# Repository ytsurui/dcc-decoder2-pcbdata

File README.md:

# ATtiny1606 DCC Decoder PCB Data

NMRA規格の信号を受信して動作する、DCCデコーダの基板設計データです。

主にNゲージ鉄道模型への搭載を想定して小型に設計しております。

## すべての基板に共通するスペック
  * 走行用モーター出力
  * BEMF読み取りによるフィードバック制御に対応
  * 最大7ファンクション出力
  * BiDi (Railcom) 出力
  * (試験的実装) Asymmetric DCCの認識回路
  
くわしくは、各基板のデータをご覧ください。
  * [K3066RA](docs/readme-K3066.md)
  * [K3057RA](docs/readme-K3057.md)
  * [M02F7RA Roomlight-N](docs/readme-roomlight-n.md)
  * [M02F7RA](docs/readme-normal.md)

## 閲覧・編集に必要なCAD (開発環境)
  * KiCad Version (5.1.9)-1 (またはそれ以降)

## 回路図

  * [v2021-04](https://github.com/ytsurui/dcc-decoder2-pcbdata/releases/tag/v2021-04)

## 対応するファームウェア
  * [ATtiny1606 DCC Decoder Firmware](https://github.com/ytsurui/dcc-decoder2-firmware)

このリポジトリに含まれる、すべての種類のデコーダが上記のファームウェアで動くように設計されています。

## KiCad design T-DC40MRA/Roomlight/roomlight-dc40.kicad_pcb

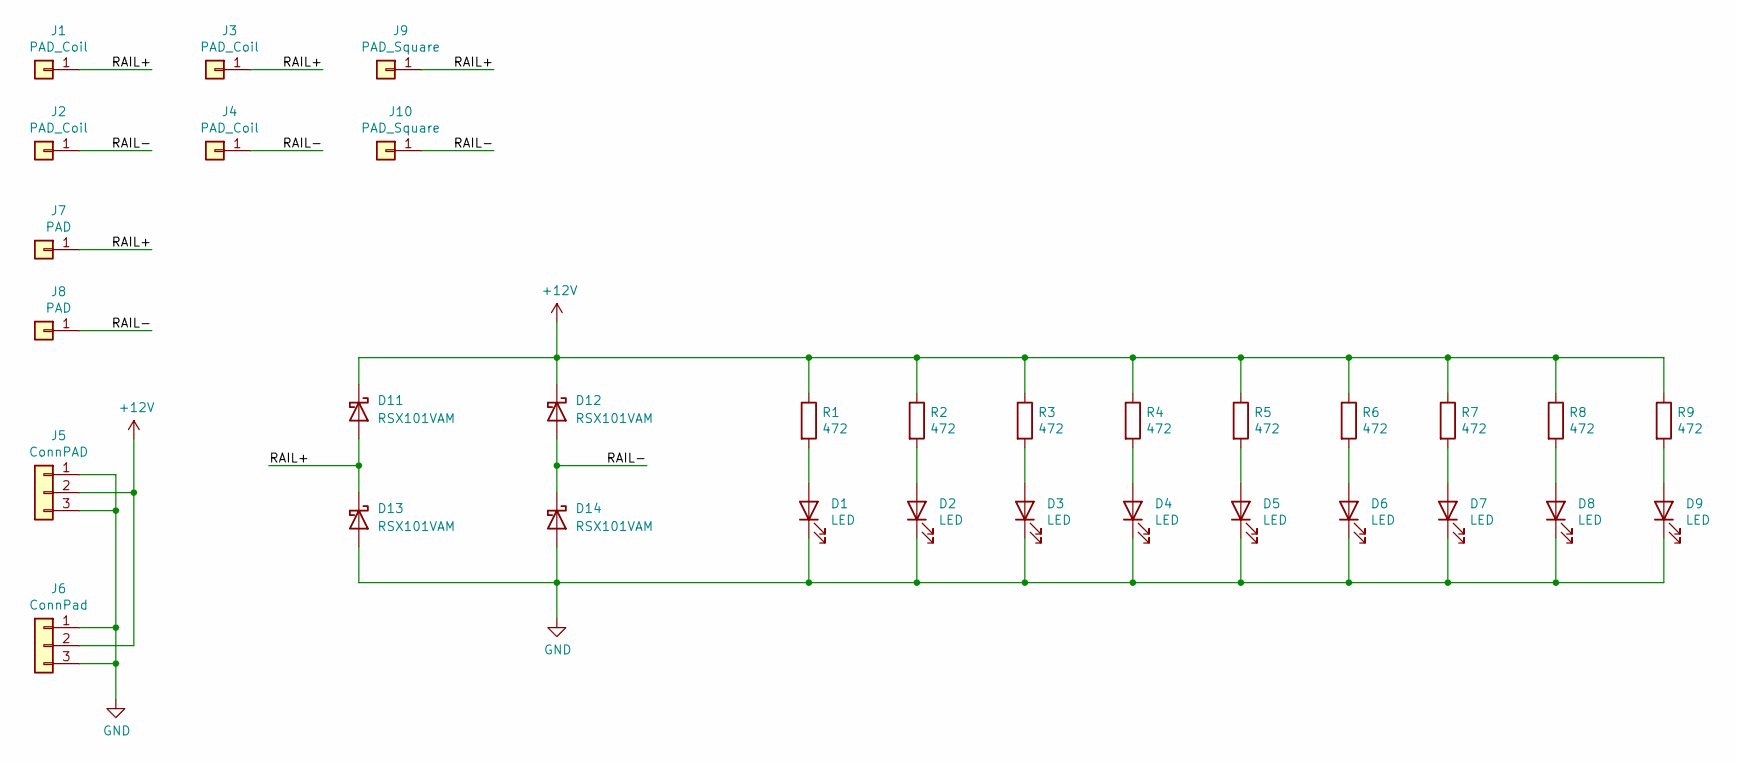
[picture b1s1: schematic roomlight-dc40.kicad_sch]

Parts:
D1, D2, D3, D4, D5, D6, D7, D8, D9: LED; LED_1608_SLIMPAD
D11, D12, D13, D14: RSX101VAM; TUMD2M
J1, J2, J3, J4: PAD_Coil; PAD_COIL_1.3x1.3_NoHole
J5: ConnPAD; PCB_CONN_PAD_3pin_2.5mmx1.2mm_SMD
J6: ConnPad; PCB_CONN_PAD_3pin_2.5mmx1.2mm_SMD
J7, J8: PAD; PAD_1.0x1.8_SMD
J9, J10: PAD_Square; PAD_Square_1.3x1.3_Hole0.8
R1, R2, R3, R4, R5, R6, R7, R8, R9: 472; R_1608_20240411

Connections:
+12V: D11.1 (K), D12.1 (K), J5.2, J6.2, R1.1, R2.1, R3.1, R4.1, R5.1, R6.1, R7.1, R8.1, R9.1
/RAIL+: D11.2 (A), D13.1 (K), J1.1, J3.1, J7.1, J9.1
/RAIL-: D12.2 (A), D14.1 (K), J2.1, J4.1, J8.1, J10.1
GND: D1.1 (K), D2.1 (K), D3.1 (K), D4.1 (K), D5.1 (K), D6.1 (K), D7.1 (K), D8.1 (K), D9.1 (K), D13.2 (A), D14.2 (A), J5.1, J5.3, J6.1, J6.3
unnamed: D1.2 (A), R1.2
unnamed: D2.2 (A), R2.2
unnamed: D3.2 (A), R3.2
unnamed: D4.2 (A), R4.2
unnamed: D5.2 (A), R5.2
unnamed: D6.2 (A), R6.2
unnamed: D7.2 (A), R7.2
unnamed: D8.2 (A), R8.2
unnamed: D9.2 (A), R9.2

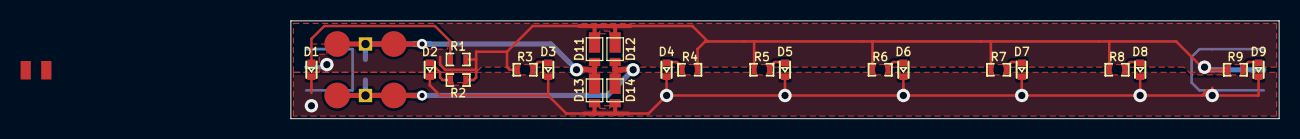
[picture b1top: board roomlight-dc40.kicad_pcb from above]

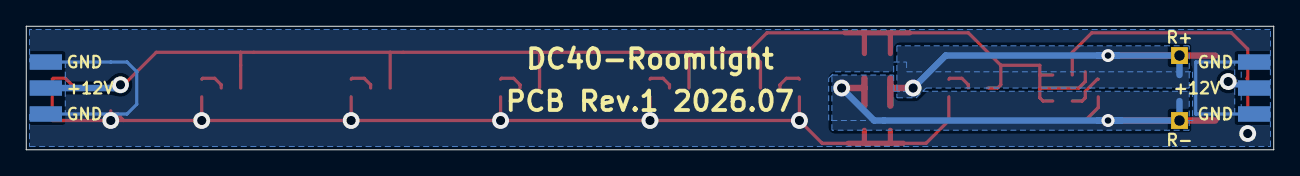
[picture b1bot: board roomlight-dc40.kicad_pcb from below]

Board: 2 copper layers, 96.0 x 9.5 mm, 32 parts (2 on the bottom side), 13 nets.

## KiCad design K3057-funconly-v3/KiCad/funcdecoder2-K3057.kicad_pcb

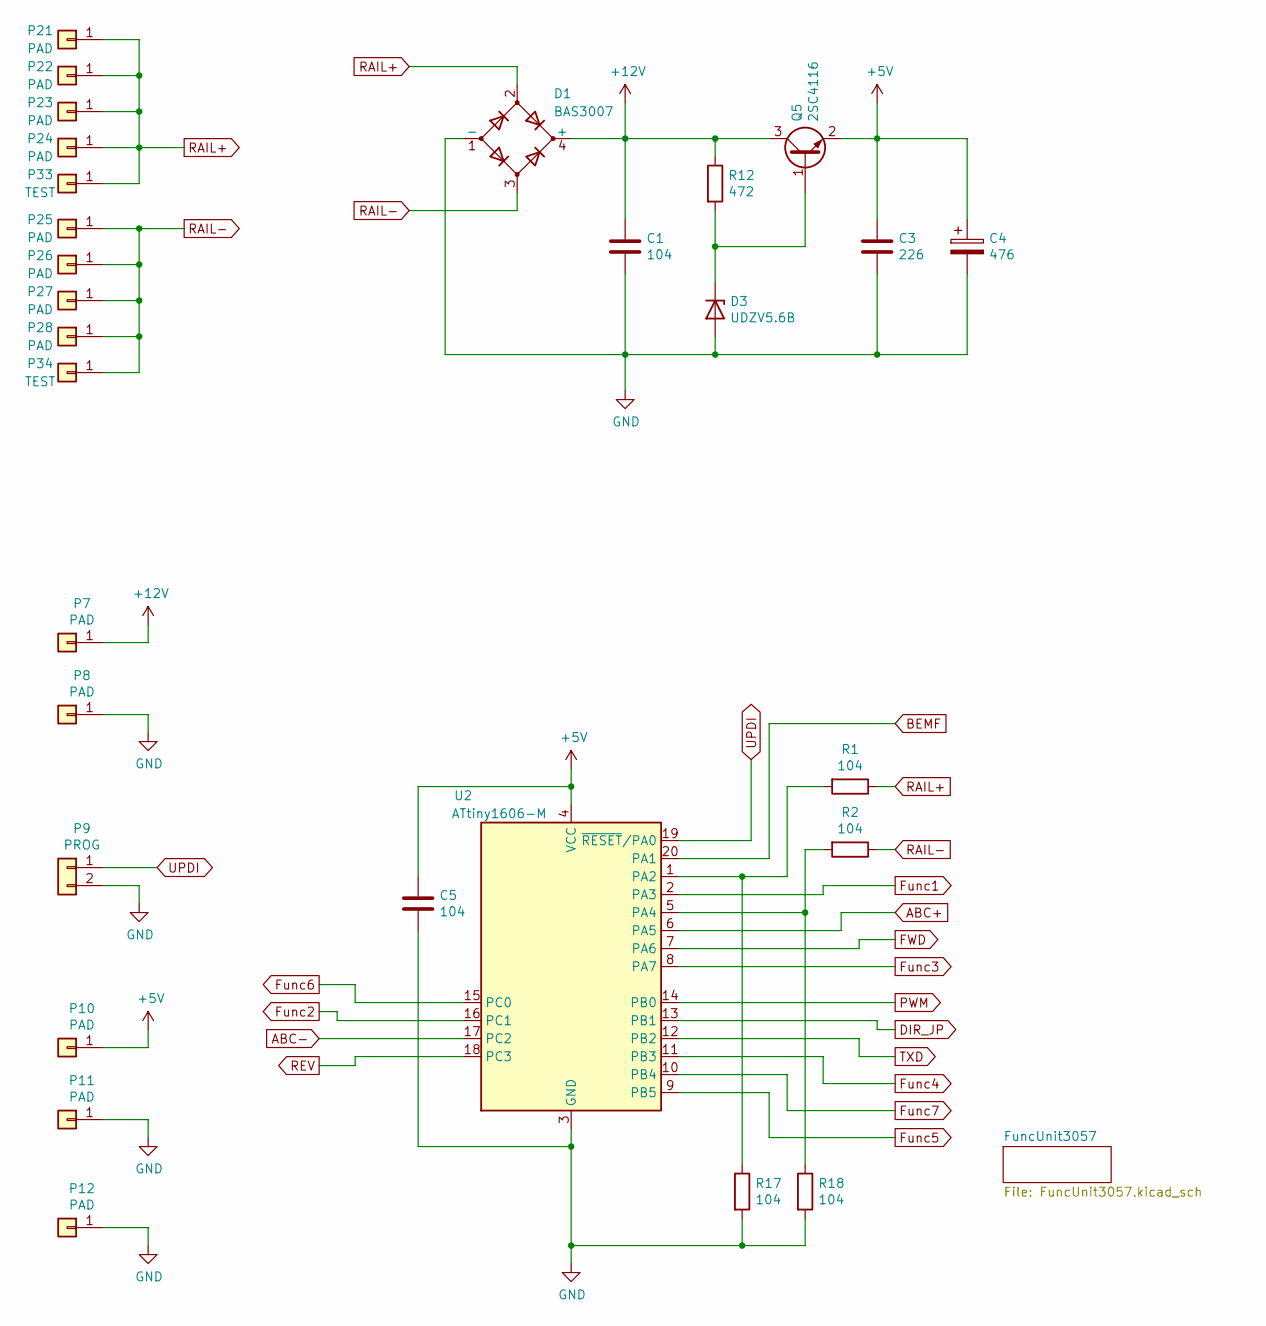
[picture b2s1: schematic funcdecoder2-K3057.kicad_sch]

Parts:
C1, C5: 104; C_1005_v4
C3: 226; C_1608_v4
C4: 476; CP_1608
D1: BAS3007; SOT-143
D3: UDZV5.6B; UMD2
P7: PAD; PAD_1.0x1.8_SMD
P8, P10: PAD; PAD_0.6x1.0_SMD
P9: PROG; PAD_PROG_2PIN_HOLE0.7
P11: PAD; PAD_0.5x1.2_SMD
P12: PAD; PAD_1.0x1.4_SMD
P21, P24, P25, P28: PAD; KATO_RAILPAD_3057_8mm
P22, P23, P26, P27: PAD; KATO_RAILPAD_3057_7mm
P33, P34: TEST; PAD_1.2x1.2_Hole0.7
Q5: 2SC4116; SC-70_v2
R1, R2, R17, R18: 104; R_1608_20240411
R12: 472; R_1608_20240411
U2: ATtiny1606-M; VQFN-20-1EP_3x3mm_P0.4mm_EP1.7x1.7mm

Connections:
+5V: C3.1, C4.1, C5.1, P10.1, Q5.2 (E), U2.4 (VCC)
+12V: C1.1, D1.4 (+), P7.1, Q5.3 (C), R12.1; also elsewhere on the board
ABC+: U2.6 (PA5)
ABC-: U2.17 (PC2)
BEMF: U2.20 (PA1)
DIR_JP: U2.13 (PB1); also elsewhere on the board
FWD: U2.7 (PA6)
Func1: U2.2 (PA3); also elsewhere on the board
Func2: U2.16 (PC1); also elsewhere on the board
Func3: U2.8 (PA7); also elsewhere on the board
Func4: U2.11 (PB3); also elsewhere on the board
Func5: U2.9 (PB5); also elsewhere on the board
Func6: U2.15 (PC0); also elsewhere on the board
Func7: U2.10 (PB4); also elsewhere on the board
GND: C1.2, C3.2, C4.2, C5.2, D1.1 (-), D3.2 (A), P8.1, P9.2, P11.1, P12.1, R17.2, R18.2, U2.3 (GND), U2.21 (GND); also elsewhere on the board
unnamed: D3.1 (K), Q5.1 (B), R12.2
unnamed: R1.2, R17.1, U2.1 (PA2)
unnamed: R2.2, R18.1, U2.5 (PA4)
PWM: U2.14 (PB0)
RAIL+: D1.2, P21.1, P22.1, P23.1, P24.1, P33.1, R1.1
RAIL-: D1.3, P25.1, P26.1, P27.1, P28.1, P34.1, R2.1
REV: U2.18 (PC3)
TXD: U2.12 (PB2)
UPDI: P9.1, U2.19 (~RESET/PA0)

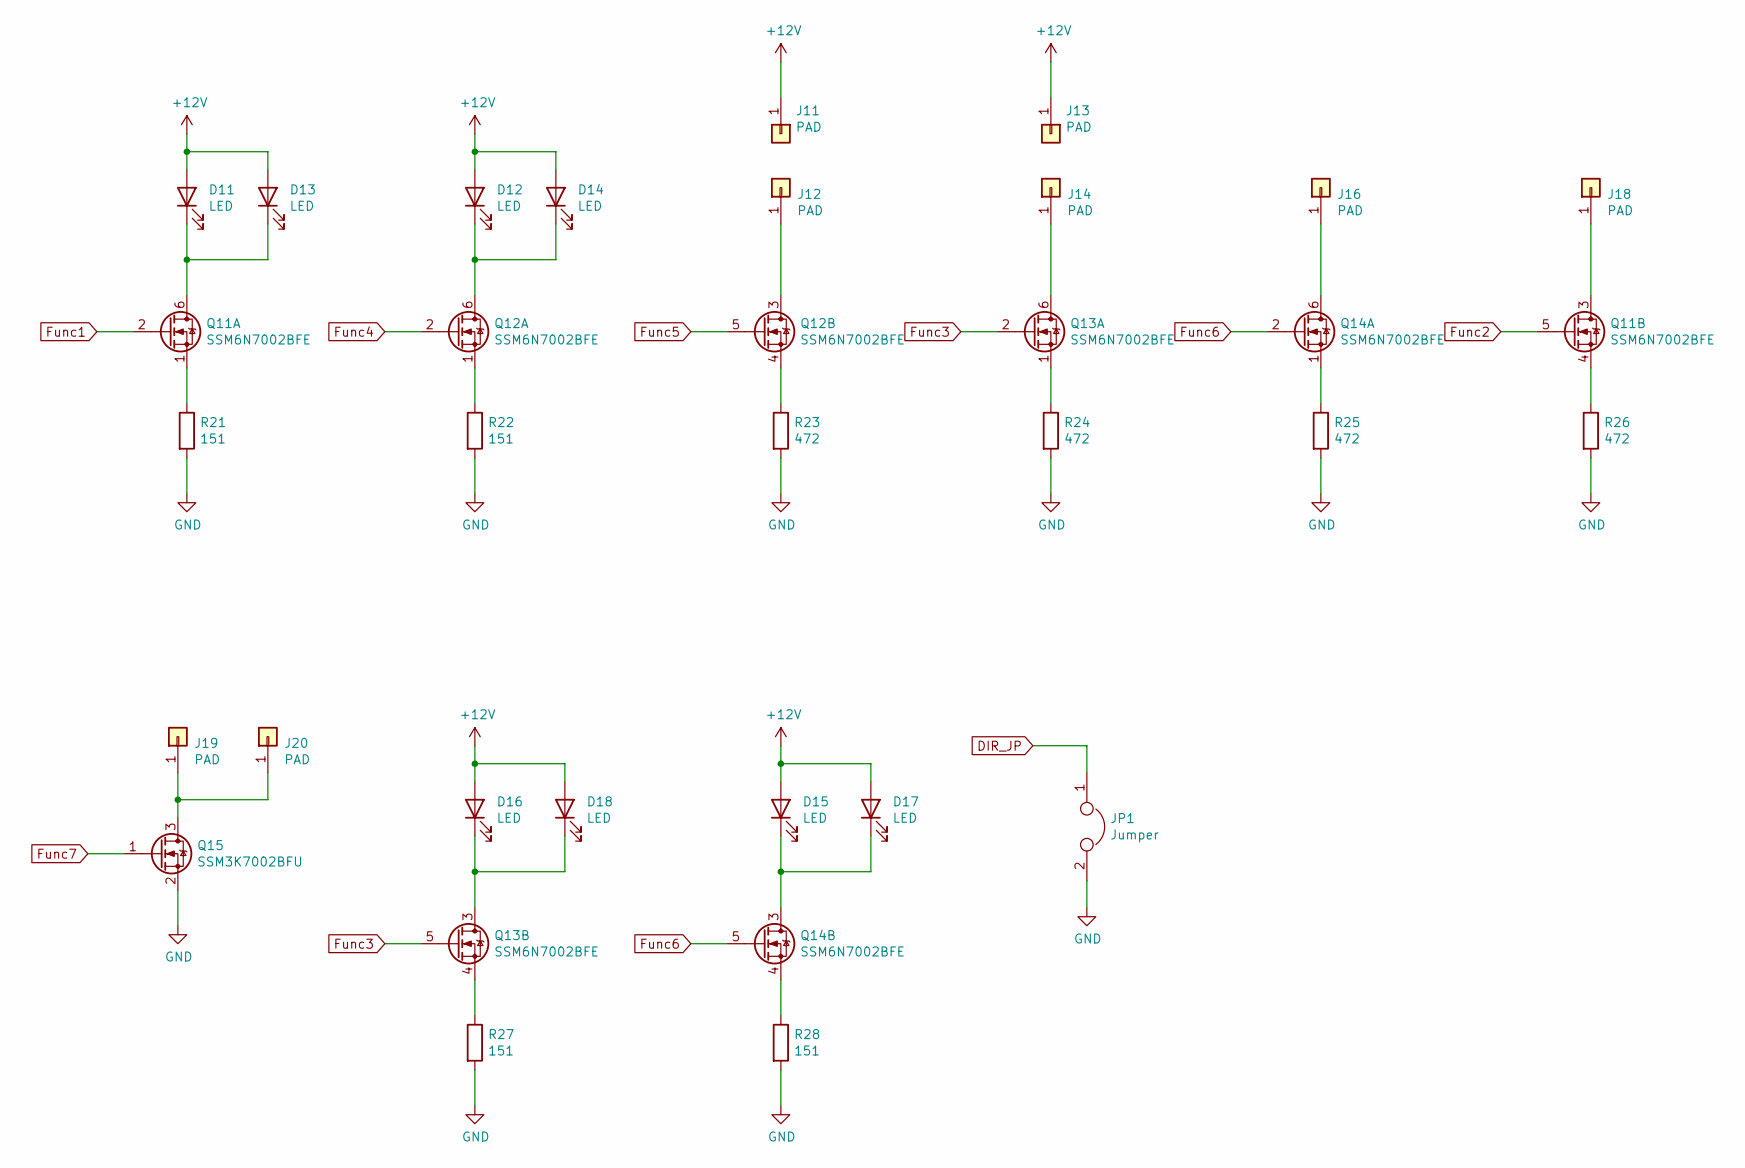
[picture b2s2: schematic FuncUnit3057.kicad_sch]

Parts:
D11, D12, D13, D14, D15, D16, D17, D18: LED; LED_1224_1005_SIDE_BIG2
J11, J13: PAD; PAD_1.0x1.8_SMD
J12, J14, J16, J18: PAD; PAD_1.0x1.0_Hole0.6
J19: PAD; PAD_1.0x1.4_SMD
J20: PAD; PAD_0.5x1.2_SMD
JP1: Jumper; SOLDER_CONN_PAD_2_1.5mm
Q11, Q12, Q13, Q14: SSM6N7002BFE; SOT-666-nomark-v2
Q15: SSM3K7002BFU; SC-70_v2
R21, R22, R27, R28: 151; R_1608_20240411
R23, R25: 472; R_1005_20240411
R24, R26: 472; R_1608_20240411

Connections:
+12V: D11.2 (A), D12.2 (A), D13.2 (A), D14.2 (A), D15.2 (A), D16.2 (A), D17.2 (A), D18.2 (A), J11.1, J13.1; also elsewhere on the board
DIR_JP: JP1.1; also elsewhere on the board
Func1: Q11.2 (G); also elsewhere on the board
Func2: Q11.5 (G); also elsewhere on the board
Func3: Q13.2 (G), Q13.5 (G); also elsewhere on the board
Func4: Q12.2 (G); also elsewhere on the board
Func5: Q12.5 (G); also elsewhere on the board
Func6: Q14.2 (G), Q14.5 (G); also elsewhere on the board
Func7: Q15.1 (G); also elsewhere on the board
GND: JP1.2, Q15.2 (S), R21.2, R22.2, R23.2, R24.2, R25.2, R26.2, R27.2, R28.2; also elsewhere on the board
unnamed: D11.1 (K), D13.1 (K), Q11.6 (D)
unnamed: D12.1 (K), D14.1 (K), Q12.6 (D)
unnamed: D15.1 (K), D17.1 (K), Q14.3 (D)
unnamed: D16.1 (K), D18.1 (K), Q13.3 (D)
unnamed: J12.1, Q12.3 (D)
unnamed: J14.1, Q13.6 (D)
unnamed: J16.1, Q14.6 (D)
unnamed: J18.1, Q11.3 (D)
unnamed: J19.1, J20.1, Q15.3 (D)
unnamed: Q11.1 (S), R21.1
unnamed: Q11.4 (S), R26.1
unnamed: Q12.1 (S), R22.1
unnamed: Q12.4 (S), R23.1
unnamed: Q13.1 (S), R24.1
unnamed: Q13.4 (S), R27.1
unnamed: Q14.1 (S), R25.1
unnamed: Q14.4 (S), R28.1

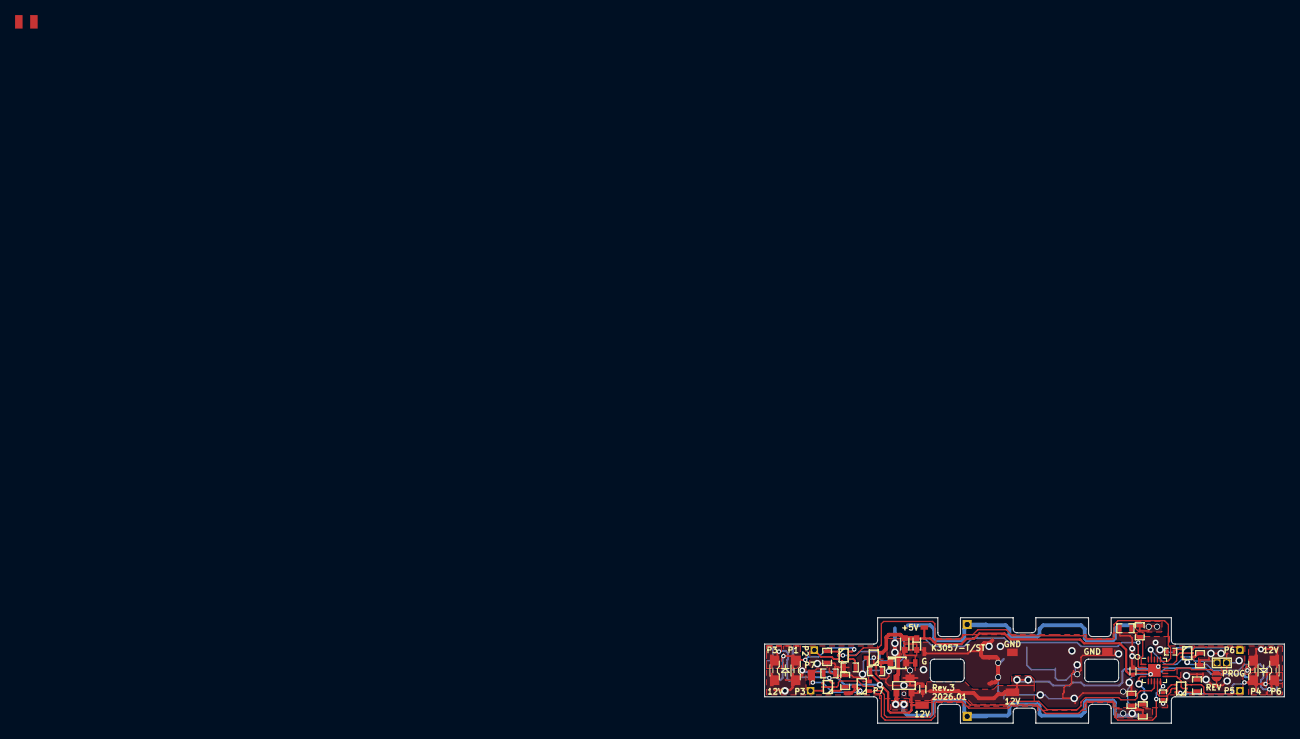
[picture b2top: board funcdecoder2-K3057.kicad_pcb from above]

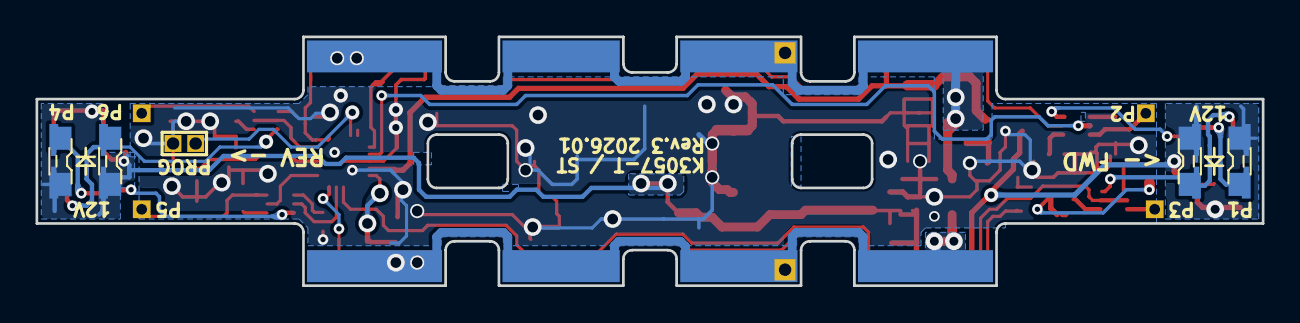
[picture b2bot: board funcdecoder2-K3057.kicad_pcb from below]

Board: 2 copper layers, 69.0 x 14.0 mm, 61 parts (4 on the bottom side), 34 nets.

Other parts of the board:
P7#2: PAD; PAD_1.0x1.8_SMD
P12#2: PAD; PAD_1.0x1.4_SMD

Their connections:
+12V: P7#2.1; also elsewhere on the board
GND: P12#2.1; also elsewhere on the board

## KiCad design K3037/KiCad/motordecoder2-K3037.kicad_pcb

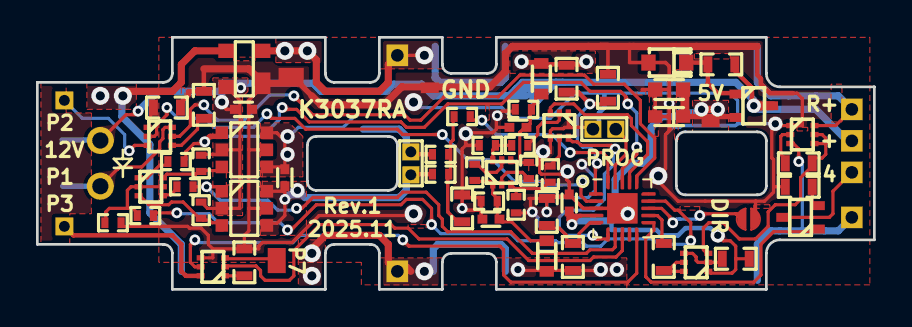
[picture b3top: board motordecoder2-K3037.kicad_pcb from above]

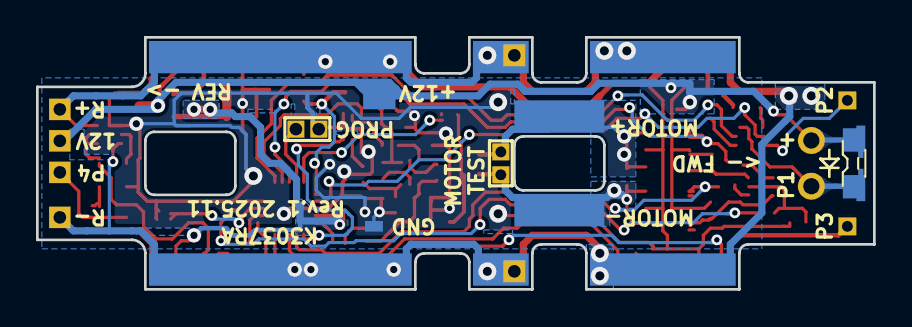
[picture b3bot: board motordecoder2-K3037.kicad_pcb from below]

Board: 2 copper layers, 46.5 x 14.0 mm, 80 parts (3 on the bottom side), 51 nets.

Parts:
C1, C5: 104; C_1005_v4
C3: 226; C_1608_v4
C4: 476; CP_1608
C7: 103; C_1005_v4
C11, C12: 105; C_1005_v4
D1: BAS3007; SOT-143
D5: UDZV5.6B; UMD2
D11: LED; LED_1224_1005_SIDE_BIG2
D13: LED; LED_3mm_HOLE
D21, D22: BAT43XV2; EMD2_small
J11: PAD; PAD_1.0x1.8_SMD
J14, J18: PAD; PAD_1.0x1.0_Hole0.6
J19: PAD; PAD_1.0x1.4_SMD
J21, J22: LED; PAD_1.2x1.2_Hole0.7
JP1: Jumper; SOLDER_CONN_PAD_2_1.5mm
P8, P10, P11: PAD; PAD_0.6x1.0_SMD
P9: PROG; PAD_PROG_2PIN_HOLE0.7
P12: PAD; PAD_1.0x1.4_SMD
P21, P25: PAD; KATO_RAILPAD_3037_8_5mm
P22, P26: PAD; KATO_RAILPAD_3037_3mm
P23, P27: PAD; KATO_RAILPAD_3037_15mm
P24, P28: JUMPER; PAD_1.2x1.2_Hole0.7
P29, P31: PAD; KATO_MOTORPAD_3037_5mm
P32: TEST; PAD_2mm_2PIN_HOLE0.6
P33, P34: TEST; PAD_1.2x1.2_Hole0.7
Q1, Q2: DMG6601LVT; SOT-23-6-wide
Q3, Q8: PMBT3904VS; SOT-666-nomark-v2
Q5: 2SC4116; SC-70_v2
Q6, Q21: PMBT3906VS; SOT-666-nomark-v2
Q11, Q13, Q22: SSM6N7002BFE; SOT-666-nomark-v2
Q15: SSM3K7002BFU; SC-70_v2
R1, R2, R17, R18: 104; R_1608_20240411
R3, R4, R7, R8, R11, R31, R35: 102; R_1005_20240411
R5, R6: 331; R_1005_20240411
R9, R10, R32, R33, R34, R36, R37, R38: 103; R_1005_20240411
R12, R24, R26: 472; R_1608_20240411
R13, R16: 103; R_1608_20240411
R14: 220; R_1608_20240411
R15: 682; R_1608_20240411
R21, R22: 151; R_1608_20240411
U2: ATtiny1606-M; VQFN-20-1EP_3x3mm_P0.4mm_EP1.7x1.7mm

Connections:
+5V: C3.1, C4.1, C5.1, P10.1, Q5.2 (E), Q6.1 (E1), R14.2, U2.4 (VCC)
+12V: C1.1, D1.4 (+), D11.2 (A), D13.2 (A), J11.1, J21.1, Q1.2 (S), Q2.2 (S), Q5.3 (C), R3.1, R4.1, R12.1
ABC+: Q22.6 (D), U2.6 (PA5)
ABC-: Q22.3 (D), U2.17 (PC2)
BEMF: R11.1, U2.20 (PA1)
DIR_JP: JP1.1, U2.13 (PB1)
FWD: Q2.1 (G), R6.2, U2.7 (PA6)
Func1: Q11.2 (G), U2.2 (PA3)
Func2: Q11.5 (G), U2.16 (PC1)
Func3: Q13.2 (G), U2.8 (PA7)
Func4: Q15.1 (G), U2.11 (PB3)
Func7: Q13.5 (G), U2.10 (PB4)
GND: C1.2, C3.2, C4.2, C5.2, C11.2, C12.2, D1.1 (-), D5.2 (A), JP1.2, P8.1, P9.2, P11.1, P12.1, Q1.5 (S), Q2.5 (S), Q8.1 (E1), Q13.4 (S), Q22.1 (S), Q22.4 (S), R8.2, R16.2, R17.2, R18.2, R21.2, R22.2, R24.2, R26.2, R32.2, R33.2, R36.2, R37.2, U2.3 (GND), U2.21 (GND)
MOTOR+: C7.1, P29.1, P32.1, Q1.4 (D), Q1.6 (D), R9.2
MOTOR-: C7.2, P31.1, P32.2, Q2.4 (D), Q2.6 (D), R10.2
unnamed: D5.1 (K), Q5.1 (B), R12.2
unnamed: D11.1 (K), D13.1 (K), Q11.6 (D)
unnamed: J14.1, Q13.6 (D)
unnamed: J18.1, Q11.3 (D)
unnamed: J19.1, Q13.3 (D)
unnamed: J22.1, Q15.3 (D)
unnamed: Q1.3 (G), Q3.6 (C1), R3.2
unnamed: Q2.3 (G), Q3.3 (C2), R4.2
unnamed: Q3.2 (B1), Q3.5 (B2), R7.2, R8.1
unnamed: Q3.1 (E1), R5.1
unnamed: Q3.4 (E2), R6.1
unnamed: Q6.2 (B1), Q6.4 (E2), R14.1
unnamed: Q6.5 (B2), Q6.6 (C1), R13.1
unnamed: Q6.3 (C2), Q8.4 (E2), Q8.5 (B2), R15.1
unnamed: Q8.2 (B1), R15.2
unnamed: Q11.1 (S), R21.1
unnamed: Q11.4 (S), R26.1
unnamed: Q13.1 (S), R24.1
unnamed: Q15.2 (S), R22.1
unnamed: Q21.2 (B1), R31.1
unnamed: Q21.6 (C1), R33.1, R34.2
unnamed: Q21.5 (B2), R35.1
unnamed: Q21.3 (C2), R37.1, R38.2
unnamed: Q22.2 (G), R34.1
unnamed: Q22.5 (G), R38.1
unnamed: R9.1, R10.1, R11.2, R16.1
unnamed: R1.2, R17.1, U2.1 (PA2)
unnamed: R2.2, R18.1, U2.5 (PA4)
PWM: R7.1, U2.14 (PB0)
RAIL+: D1.2, D21.2 (A), P21.1, P22.1, P23.1, P24.1, P33.1, Q8.6 (C1), R1.1
RAIL-: D1.3, D22.2 (A), P25.1, P26.1, P27.1, P28.1, P34.1, Q8.3 (C2), R2.1
REV: Q1.1 (G), R5.2, U2.18 (PC3)
TXD: R13.2, U2.12 (PB2)
UPDI: P9.1, U2.19 (~RESET/PA0)
VRAIL+: C11.1, D21.1 (K), Q21.4 (E2), R31.2, R32.1
VRAIL-: C12.1, D22.1 (K), Q21.1 (E1), R35.2, R36.1

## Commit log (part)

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2021-04-11 Fix Repositry Links
2021-04-24 回路の問題点を修正 (K3066: Rev3 / それ以外: Rev2)
2021-04-24 v2021-04へのリンクを追加
2021-05-14 基板上のF表記をP表記に変更
2021-05-14 記載内容を2021.05版に修正
2021-05-14 汎用デコーダの設計データを追加
2021-05-14 面付けデータのリンクを削除 (未作成のため)
2021-05-14 画像ファイル名間違いを修正
2022-03-10 (K3057RA) 表面のLEDパッドを増設
2022-03-10 (K3066RA v2) 形状を変更したバージョンを追加
2024-09-18 gitignoreを更新
2024-09-18 K3066RA v3の設計データを追加
2024-09-18 K3057RA v2の設計データを追加
2024-09-18 K7012RAの設計データを追加
2024-09-18 gitignoreを修正
2024-09-18 ファンクション専用デコーダの設計データを追加
